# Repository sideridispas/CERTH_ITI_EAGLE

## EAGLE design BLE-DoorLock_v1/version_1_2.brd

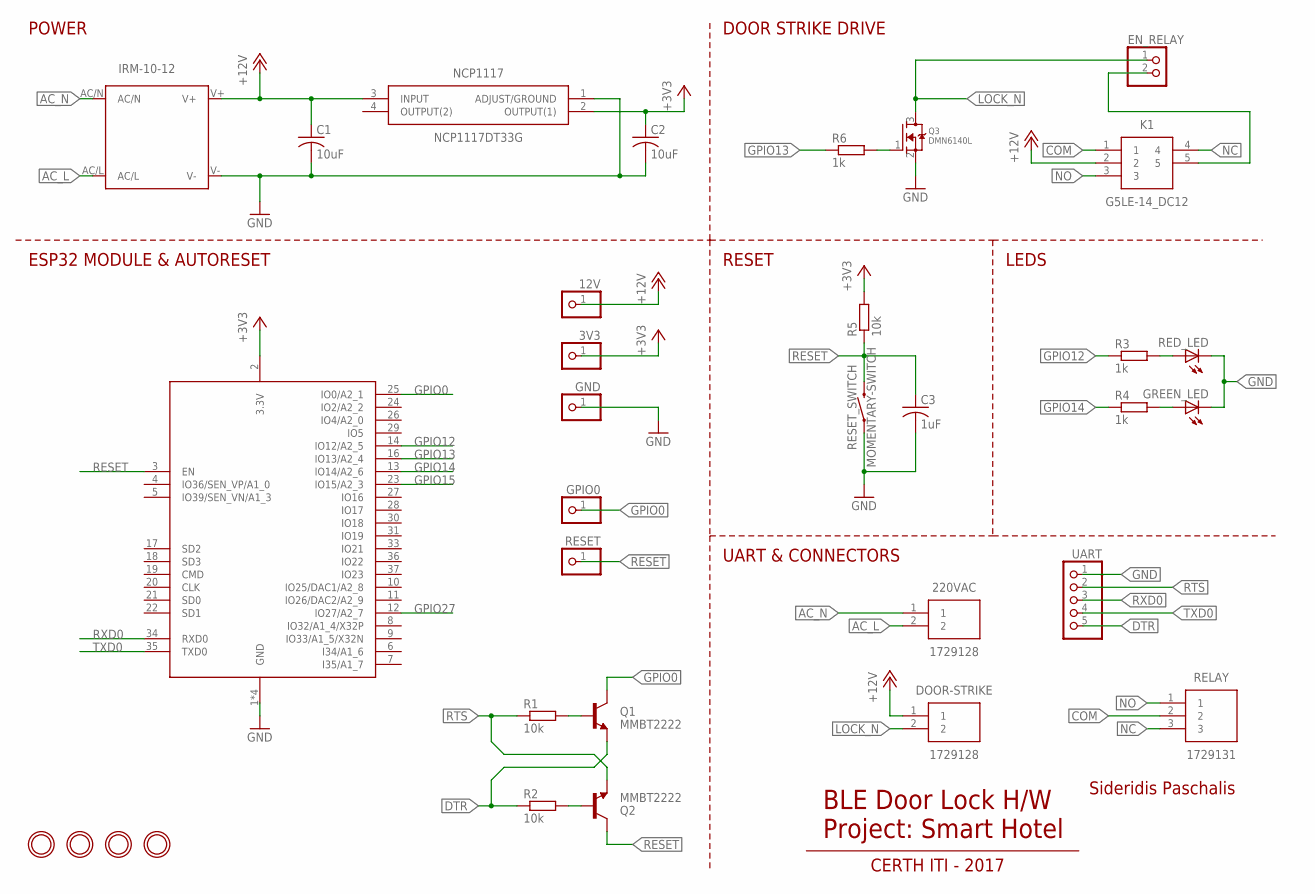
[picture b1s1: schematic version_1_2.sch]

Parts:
3V3, 12V: PINHD-1X1; 1X01
220VAC: 1729128; HDRV2W110P0X508_1X2_1016X810X1
C1, C2: 10uF; C0805
C3: 1uF; C0805
DOOR-STRIKE: 1729128; HDRV2W110P0X508_1X2_1016X810X1
EN_RELAY: PINHD-1X2; 1X02
ESP32: ESP32_WROOM32_SKINNY; WROOM32_SKINNY
GND: PINHD-1X1; 1X01
GPIO0: PINHD-1X1; 1X01
GREEN_LED: LED5MM
IRM-10-12: IRM_05/10
K1: G5LE-14_DC12; G5LE-1A
NCP1117: NCP1117DT33G; TO229P990X238-4N
Q1, Q2: MMBT2222; SOT23
Q3: DMN6140L; SOT23
R1, R2, R5: 10k; R0805
R3, R4, R6: 1k; R0805
RED_LED: LED5MM
RELAY: 1729131; SHDR3W110P0X508_1X3_1524X810X1
RESET: PINHD-1X1; 1X01
RESET_SWITCH: MOMENTARY-SWITCH; TACTILE_SWITCH_SMD_6.2MM_TALL
U$1, U$2, U$3, U$4: MOUNTINGHOLE2.5; MOUNTINGHOLE_2.5_PLATED
UART: PINHD-1X5; 1X05

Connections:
+3V3: 3V3.1, C2.1, ESP32.2 (3.3V), NCP1117.2 (OUTPUT(1)), R5.2
+12V: 12V.1, C1.1, DOOR-STRIKE.1, IRM-10-12.V+, K1.2, NCP1117.3 (INPUT)
AC_L: 220VAC.2, IRM-10-12.AC/L
AC_N: 220VAC.1, IRM-10-12.AC/N
COM: K1.1, RELAY.2
DTR: Q1.2 (E), R2.1, UART.5
GND: C1.2, C2.2, C3.2, ESP32.1 (GND), ESP32.15 (GND), ESP32.38 (GND), ESP32.P$1 (GND), GND.1, GREEN_LED.K (C), IRM-10-12.V-, NCP1117.1 (ADJUST/GROUND), Q3.2 (S), RED_LED.K (C), RESET_SWITCH.A2 (1), UART.1
GPIO0: ESP32.25 (IO0/A2_1), GPIO0.1, Q1.3 (C)
GPIO12: ESP32.14 (IO12/A2_5), R3.1
GPIO13: ESP32.16 (IO13/A2_4), R6.1
GPIO14: ESP32.13 (IO14/A2_6), R4.1
GPIO15: ESP32.23 (IO15/A2_3)
GPIO27: ESP32.12 (IO27/A2_7)
LOCK_N: DOOR-STRIKE.2, EN_RELAY.1, Q3.3 (D)
unnamed: R3.2, RED_LED.A
unnamed: Q1.1 (B), R1.2
unnamed: Q2.1 (B), R2.2
unnamed: GREEN_LED.A, R4.2
unnamed: Q3.1 (G), R6.2
unnamed: EN_RELAY.2, K1.5
NC: K1.4, RELAY.3
NO: K1.3, RELAY.1
RESET: C3.1, ESP32.3 (EN), Q2.3 (C), R5.1, RESET.1, RESET_SWITCH.B2 (2)
RTS: Q2.2 (E), R1.1, UART.2
RXD0: ESP32.34 (RXD0), UART.3
TXD0: ESP32.35 (TXD0), UART.4

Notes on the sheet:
Sideridis Paschalis
BLE Door Lock H/W Project: Smart Hotel
CERTH ITI - 2017
POWER
ESP32 MODULE & AUTORESET
DOOR STRIKE DRIVE
UART & CONNECTORS
RESET
LEDS

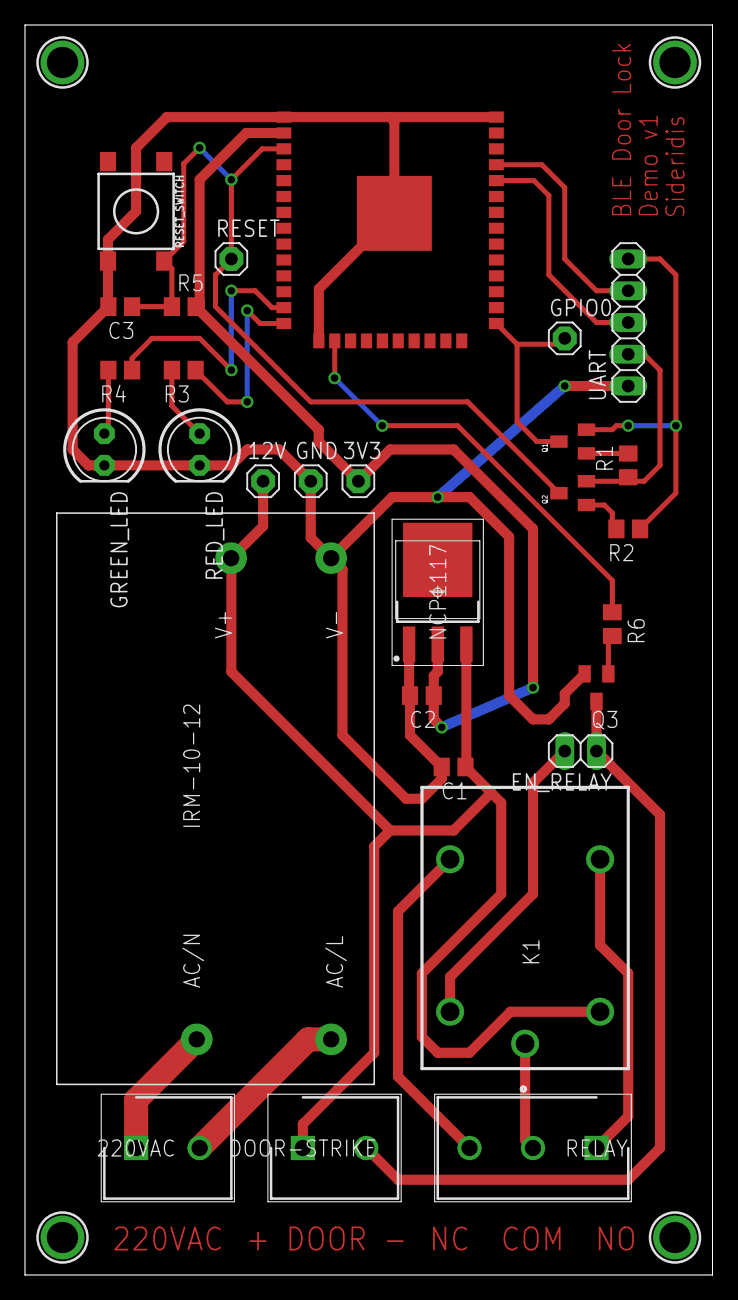
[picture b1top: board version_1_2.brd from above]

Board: 2 copper layers, 55.0 x 100.0 mm, 33 parts (0 on the bottom side), 24 nets.

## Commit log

2017-10-31 First try
2017-10-31 REPO OK
2017-11-01 First version for prototype PCB, 12VDC ONLY
2017-11-01 Before adding the relay
2017-11-01 New board with RELAY. NOT NETTED YET just layout
2017-11-02 Demo PCB -with relay- version_1.2

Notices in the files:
parts and their libraries:
SparkFun-Switches: Licensing: Creative Commons ShareAlike 4.0 International - https://creativecommons.org/licenses/by-sa/4.0
